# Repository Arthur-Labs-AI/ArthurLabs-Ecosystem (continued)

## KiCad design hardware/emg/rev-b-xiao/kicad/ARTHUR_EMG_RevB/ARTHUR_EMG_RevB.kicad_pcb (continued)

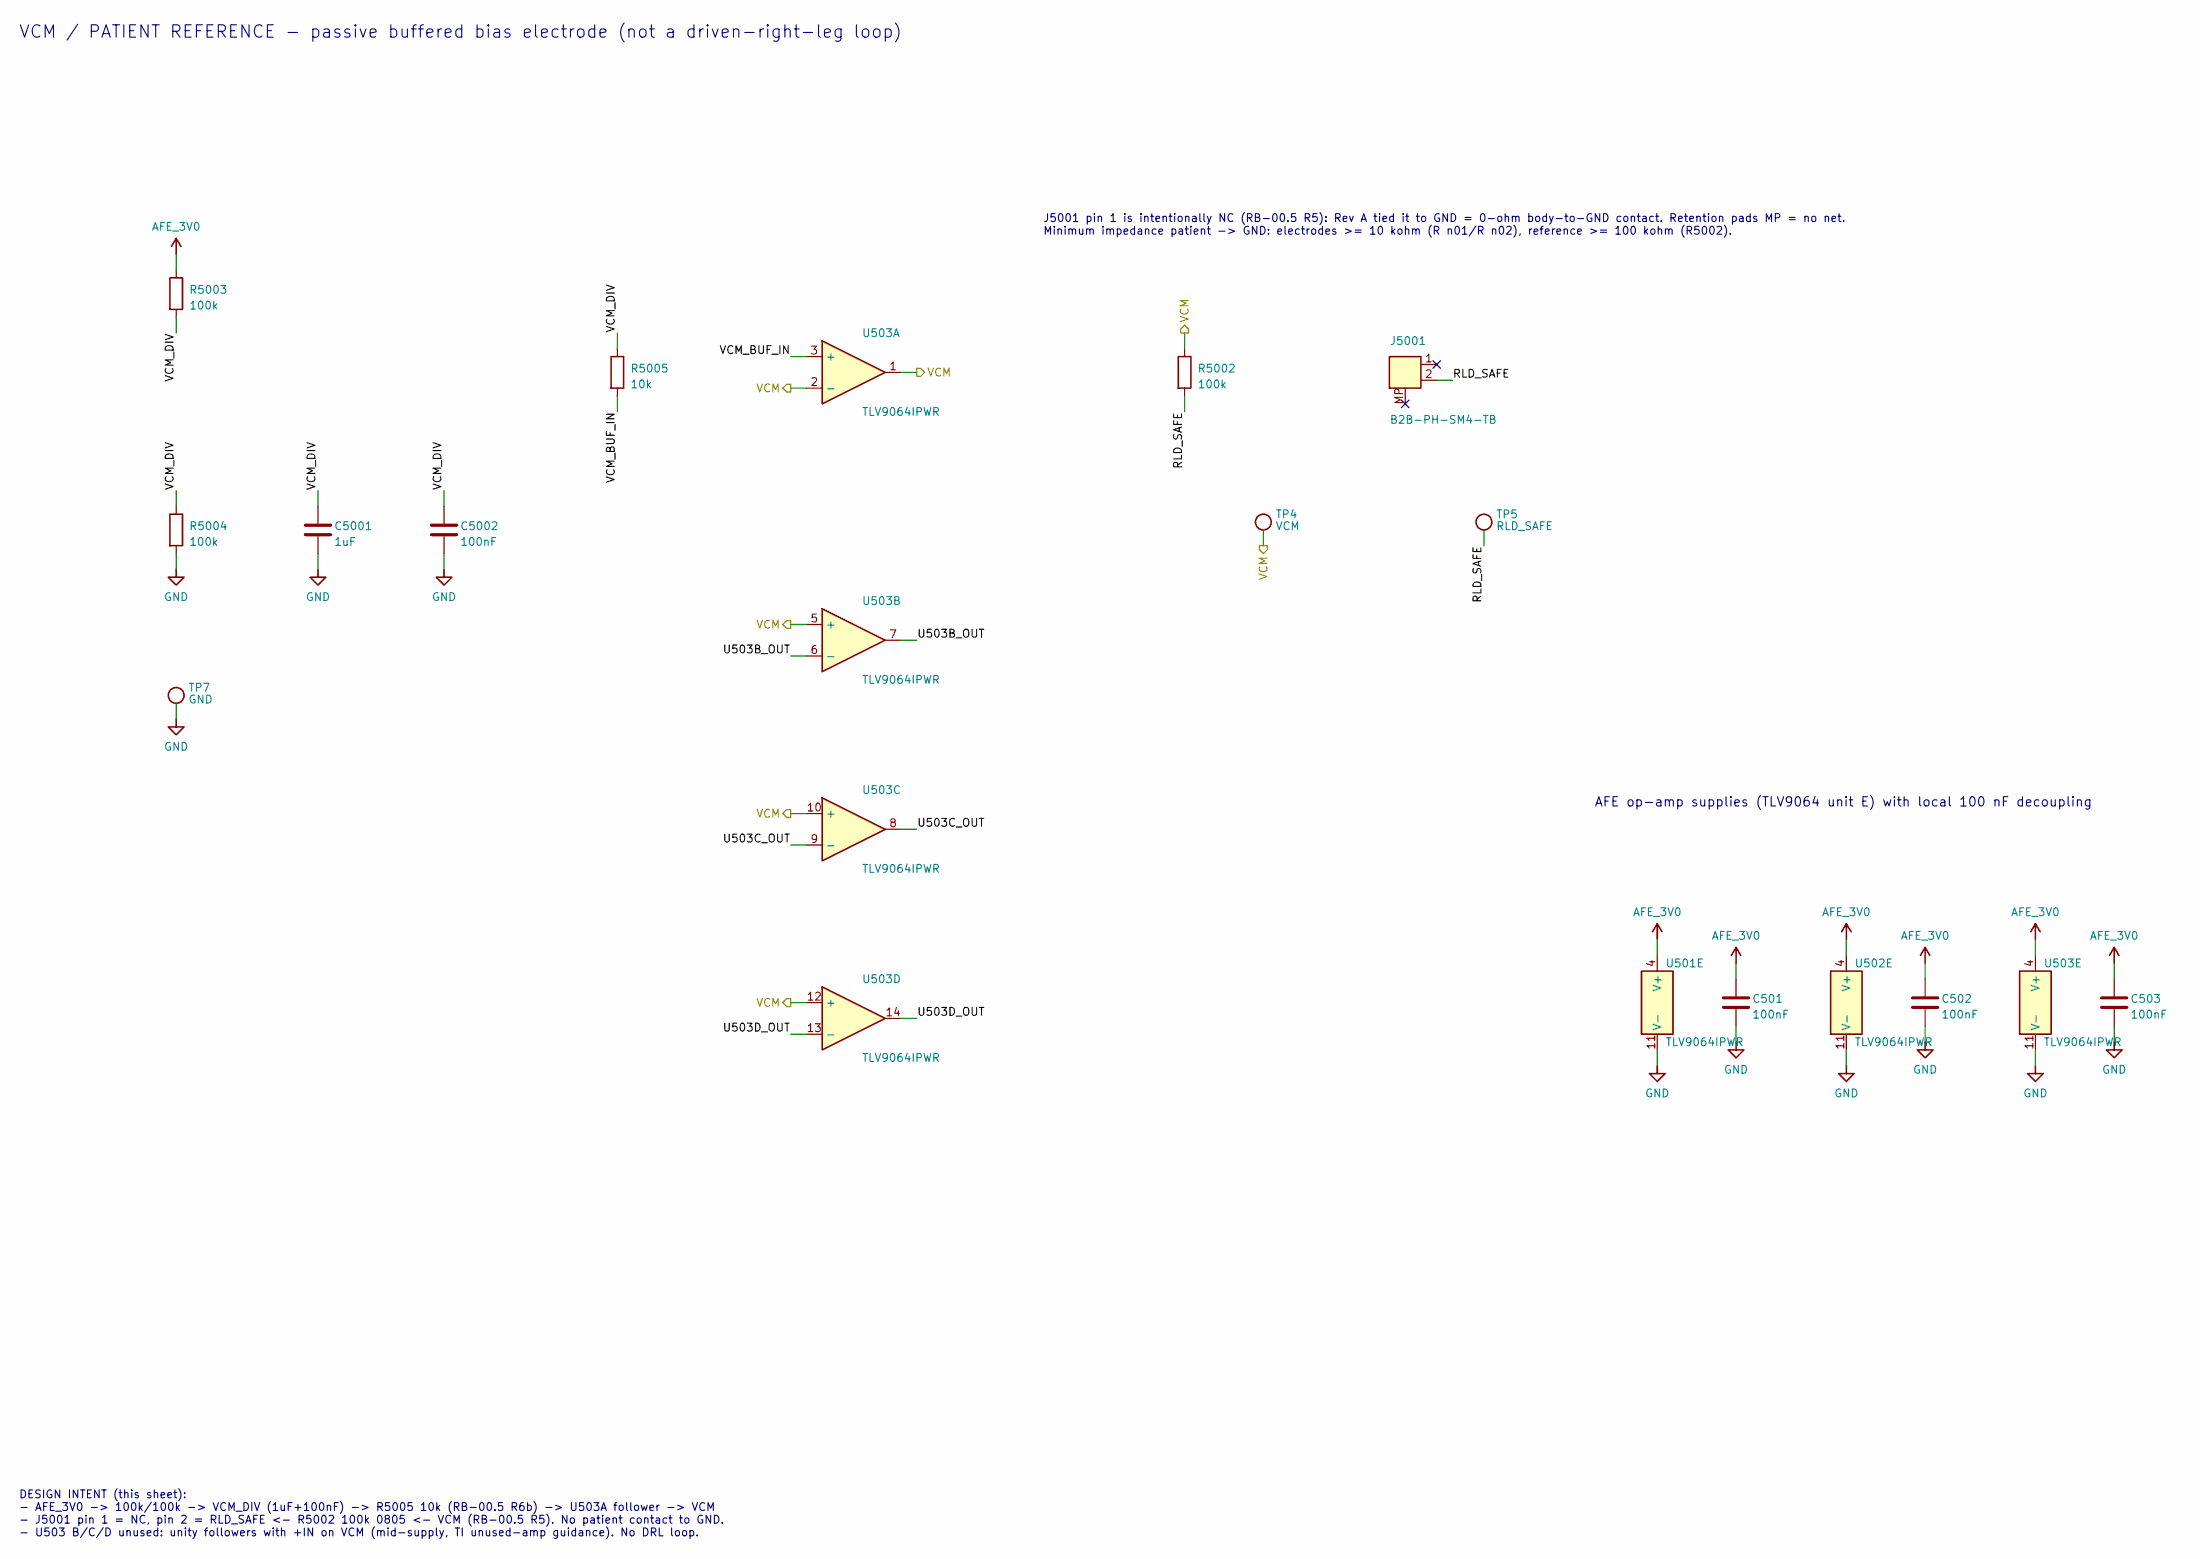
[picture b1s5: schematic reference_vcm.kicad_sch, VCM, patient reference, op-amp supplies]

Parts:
C501, C502, C503, C5002: 100nF; C_0603_1608Metric; MPN CC0603KRX7R9BB104; LCSC C14663
C5001: 1uF; C_0603_1608Metric; MPN CL10B105KO8NNNC; LCSC C59782
J5001: B2B-PH-SM4-TB; JST_PH_B2B-PH-SM4-TB_1x02-1MP_P2.00mm_Vertical; MPN B2B-PH-SM4-TB(LF)(SN); LCSC C160352
R5002: 100k; R_0805_2012Metric; MPN 0805W8F1003T5E; LCSC C149504
R5003, R5004: 100k; R_0603_1608Metric; MPN 0603WAF1003T5E; LCSC C25803
R5005: 10k; R_0603_1608Metric; MPN RC0603FR-0710KL; LCSC C98220
TP4: VCM; TestPoint_Pad_D1.5mm; MPN N/A (bare copper pad); JLC_Class N/A (not assembled)
TP5: RLD_SAFE; TestPoint_Pad_D1.5mm; MPN N/A (bare copper pad); JLC_Class N/A (not assembled)
TP7: GND; TestPoint_Pad_D1.5mm; MPN N/A (bare copper pad); JLC_Class N/A (not assembled)
U501, U502, U503: TLV9064IPWR; TSSOP-14_4.4x5mm_P0.65mm; MPN TLV9064IPWR; LCSC C779410

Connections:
/CH2/BUF_N: U501.13 (-), U501.14; also elsewhere on the board
/CH2/BUF_P: U501.8, U501.9 (-); also elsewhere on the board
/CH2/HIZ_N: U501.12 (+); also elsewhere on the board
/CH2/HIZ_P: U501.10 (+); also elsewhere on the board
/CH4/BUF_N: U502.13 (-), U502.14; also elsewhere on the board
/CH4/BUF_P: U502.8, U502.9 (-); also elsewhere on the board
/CH4/HIZ_N: U502.12 (+); also elsewhere on the board
/CH4/HIZ_P: U502.10 (+); also elsewhere on the board
/Reference_VCM/RLD_SAFE: J5001.2, R5002.2, TP5.1
/Reference_VCM/U503B_OUT: U503.6 (-), U503.7
/Reference_VCM/U503C_OUT: U503.8, U503.9 (-)
/Reference_VCM/U503D_OUT: U503.13 (-), U503.14
/Reference_VCM/VCM_BUF_IN: R5005.2, U503.3 (+)
/Reference_VCM/VCM_DIV: C5001.1, C5002.1, R5003.2, R5004.1, R5005.1
/VCM: R5002.1, TP4.1, U503.1, U503.2 (-), U503.5 (+), U503.10 (+), U503.12 (+); also elsewhere on the board
AFE_3V0: C501.1, C502.1, C503.1, R5003.1, U501.4 (V+), U502.4 (V+), U503.4 (V+); also elsewhere on the board
GND: C501.2, C502.2, C503.2, C5001.2, C5002.2, R5004.2, TP7.1, U501.11 (V-), U502.11 (V-), U503.11 (V-); also elsewhere on the board

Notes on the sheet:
J5001 pin 1 is intentionally NC (RB-00.5 R5): Rev A tied it to GND = 0-ohm body-to-GND contact. Retention pads MP = no net. Minimum impedance patient -> GND: electrodes >= 10 kohm (R n01/R n02), reference >= 100 kohm (R5002).
DESIGN INTENT (this sheet): - AFE_3V0 -> 100k/100k -> VCM_DIV (1uF+100nF) -> R5005 10k (RB-00.5 R6b) -> U503A follower -> VCM - J5001 pin 1 = NC, pin 2 = RLD_SAFE <- R5002 100k 0805 <- VCM (RB-00.5 R5). No patient contact to GND. - U503 B/C/D unused: unity followers with +IN on VCM (mid-supply, TI 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
VCM / PATIENT REFERENCE - passive buffered bias electrode (not a driven-right-leg loop)
AFE op-amp supplies (TLV9064 unit E) with local 100 nF decoupling

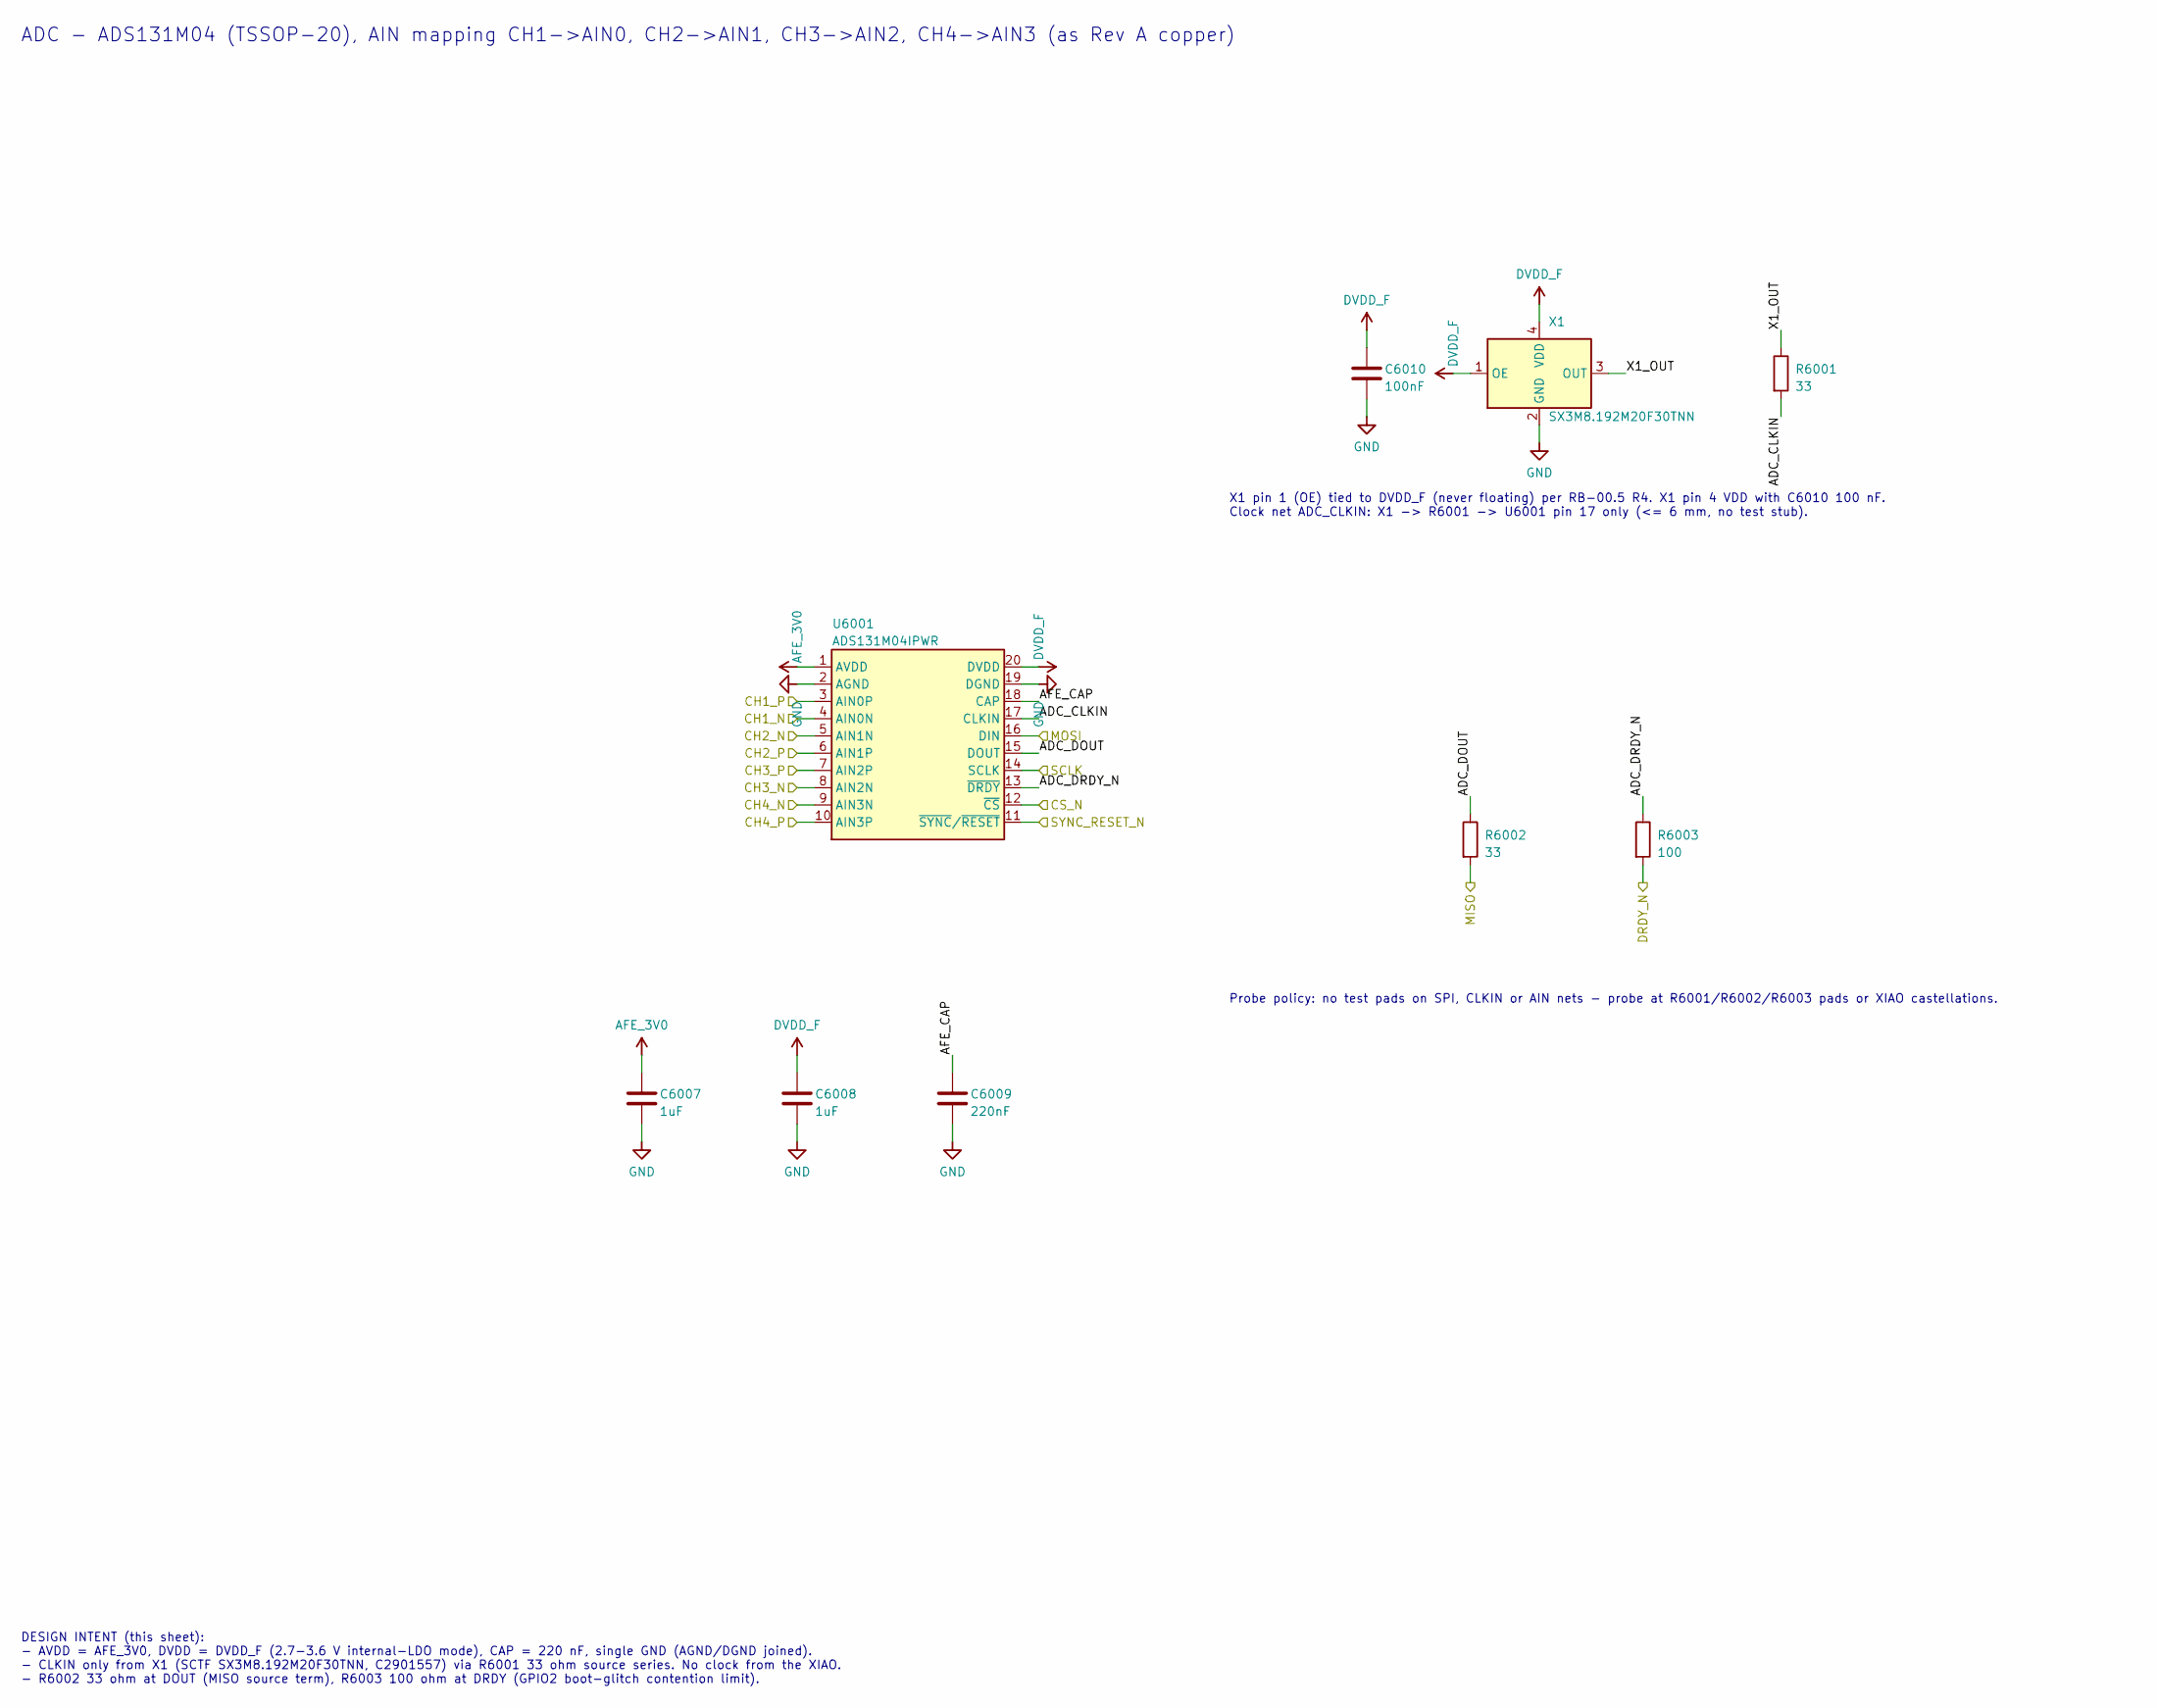
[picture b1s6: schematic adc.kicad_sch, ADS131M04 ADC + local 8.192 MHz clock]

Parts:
C6007, C6008: 1uF; C_0603_1608Metric; MPN CL10B105KO8NNNC; LCSC C59782
C6009: 220nF; C_0603_1608Metric; MPN CL10B224KO8NNNC; LCSC C160828
C6010: 100nF; C_0603_1608Metric; MPN CC0603KRX7R9BB104; LCSC C14663
R6001, R6002: 33; R_0603_1608Metric; MPN 0603WAF330JT5E; LCSC C23140
R6003: 100; R_0603_1608Metric; MPN 0603WAF1000T5E; LCSC C22775
U6001: ADS131M04IPWR; TSSOP-20_4.4x6.5mm_P0.65mm; MPN ADS131M04IPWR; LCSC C2862562
X1: SX3M8.192M20F30TNN; OSC_SCTF_SX3M_SMD3225-4P; MPN SX3M8.192M20F30TNN; LCSC C2901557

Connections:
/ADC/ADC_CLKIN: R6001.2, U6001.17 (CLKIN)
/ADC/ADC_DOUT: R6002.1, U6001.15 (DOUT)
/ADC/ADC_DRDY_N: R6003.1, U6001.13 (~DRDY)
/ADC/AFE_CAP: C6009.1, U6001.18 (CAP)
/ADC/X1_OUT: R6001.1, X1.3 (OUT)
/CH1_N: U6001.4 (AIN0N); also elsewhere on the board
/CH1_P: U6001.3 (AIN0P); also elsewhere on the board
/CH2_N: U6001.5 (AIN1N); also elsewhere on the board
/CH2_P: U6001.6 (AIN1P); also elsewhere on the board
/CH3_N: U6001.8 (AIN2N); also elsewhere on the board
/CH3_P: U6001.7 (AIN2P); also elsewhere on the board
/CH4_N: U6001.9 (AIN3N); also elsewhere on the board
/CH4_P: U6001.10 (AIN3P); also elsewhere on the board
/CS_N: U6001.12 (~CS); also elsewhere on the board
/DRDY_N: R6003.2; also elsewhere on the board
/MISO: R6002.2; also elsewhere on the board
/MOSI: U6001.16 (DIN); also elsewhere on the board
/SCLK: U6001.14 (SCLK); also elsewhere on the board
/SYNC_RESET_N: U6001.11 (~SYNC/~RESET); also elsewhere on the board
AFE_3V0: C6007.1, U6001.1 (AVDD); also elsewhere on the board
DVDD_F: C6008.1, C6010.1, U6001.20 (DVDD), X1.1 (OE), X1.4 (VDD); also elsewhere on the board
GND: C6007.2, C6008.2, C6009.2, C6010.2, U6001.2 (AGND), U6001.19 (DGND), X1.2 (GND); also elsewhere on the board

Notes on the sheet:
DESIGN INTENT (this sheet): - AVDD = AFE_3V0, DVDD = DVDD_F (2.7-3.6 V internal-LDO mode), CAP = 220 nF, single GND (AGND/DGND joined). - CLKIN only from X1 (SCTF SX3M8.192M20F30TNN, C2901557) via R6001 33 ohm source series. No clock from the XIAO. - R6002 33 ohm at DOUT (MISO source term), R6003 1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
ADC - ADS131M04 (TSSOP-20), AIN mapping CH1->AIN0, CH2->AIN1, CH3->AIN2, CH4->AIN3 (as Rev A copper)
Probe policy: no test pads on SPI, CLKIN or AIN nets - probe at R6001/R6002/R6003 pads or XIAO castellations.
X1 pin 1 (OE) tied to DVDD_F (never floating) per RB-00.5 R4. X1 pin 4 VDD with C6010 100 nF. Clock net ADC_CLKIN: X1 -> R6001 -> U6001 pin 17 only (<= 6 mm, no test stub).

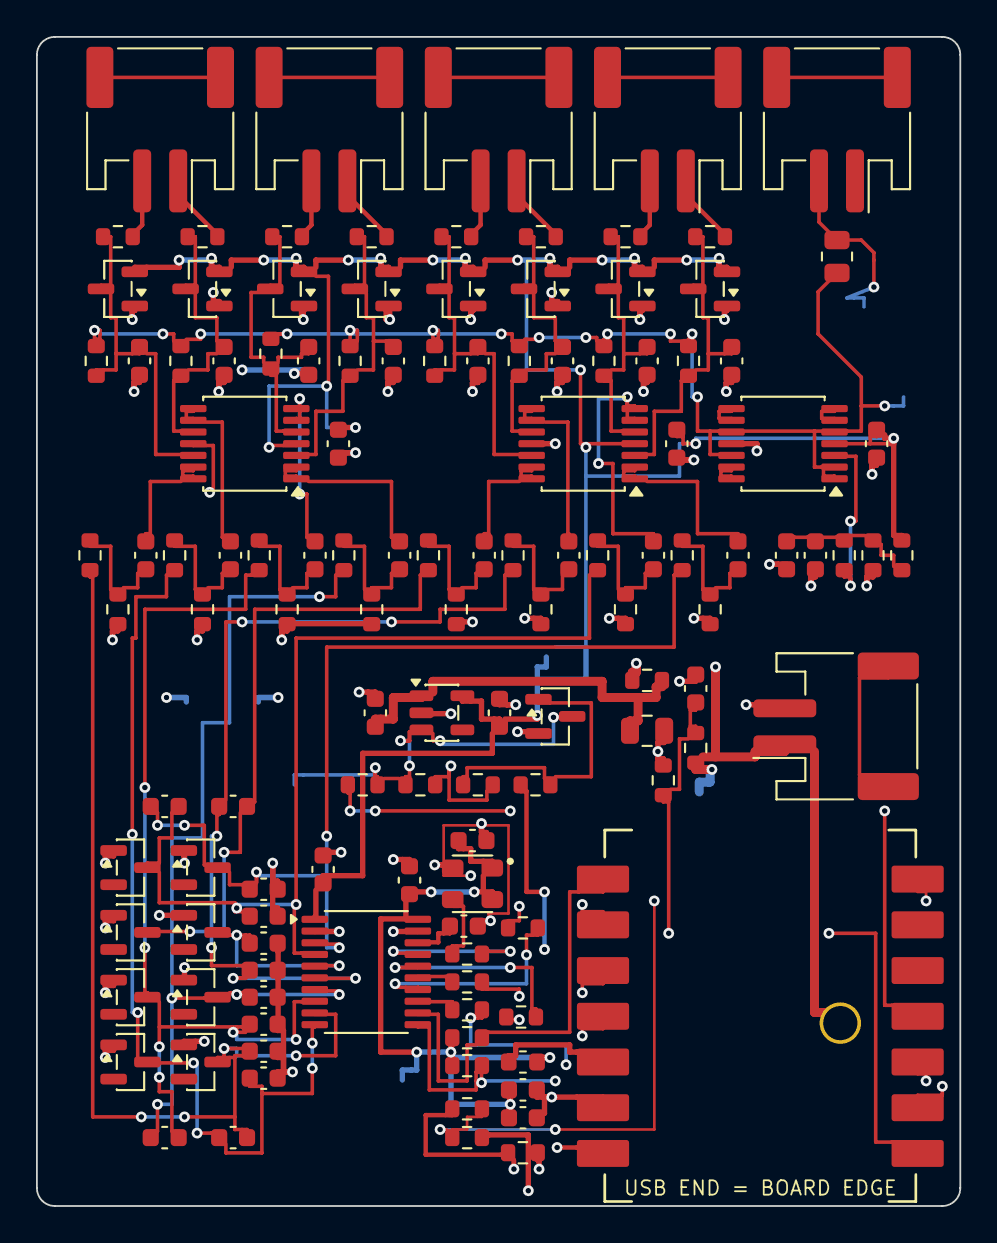
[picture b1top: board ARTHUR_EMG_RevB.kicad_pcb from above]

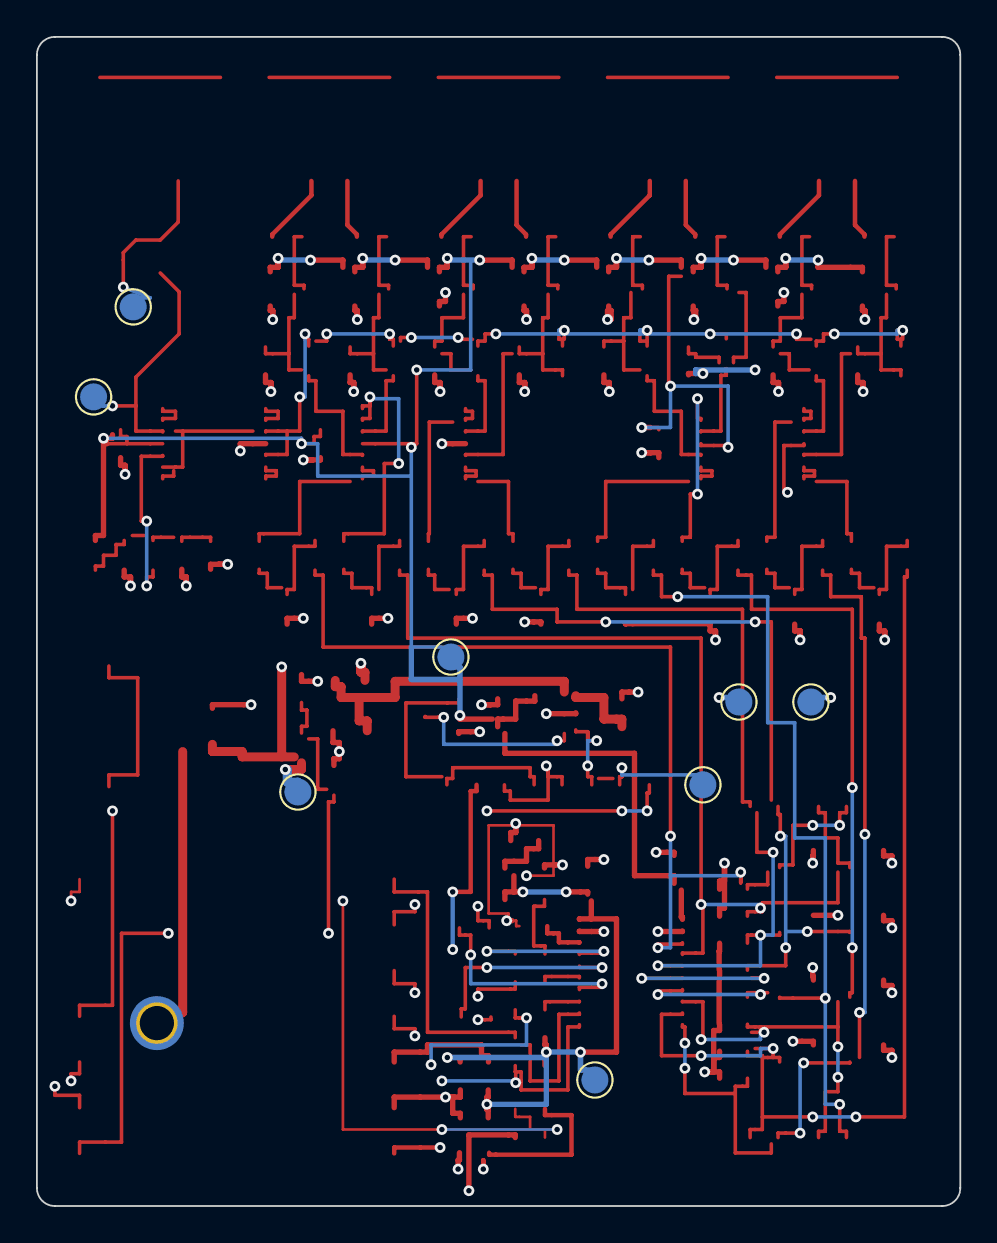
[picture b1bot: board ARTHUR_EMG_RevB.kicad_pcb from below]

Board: 4 copper layers, 51.3 x 65.0 mm, 135 parts (8 on the bottom side), 72 nets.

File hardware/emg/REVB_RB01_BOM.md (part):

# A.R.T.H.U.R EMG Rev B — RB-01 BOM

Source: `kicad-cli sch export bom` on `hardware/emg/rev-b-xiao/kicad/ARTHUR_EMG_RevB/ARTHUR_EMG_RevB.kicad_sch`, grouped by Value + Footprint + MPN + DNP (10.0.6).
**Prices are not re-quoted in RB-01**; see REVB_COST_MODEL.md. No component was substituted to reduce cost.

## Summary

| Metric | Count |
|---|---|
| Components in the netlist | 135 |
| **Populated (JLC-assembled) components** | **126** (R 53, C 43, D 16, J 6, U 5, X 1, Q 1, FB 1) |
| **DNP** | **1** (U1 XIAO ESP32S3: bought retail, hand-soldered per REVB_XIAO_ASSEMBLY_PROCEDURE.md) |
| Bare test pads (not in BOM, not in CPL) | 8 (TP1–TP8) |
| BOM lines | 30 (29 populated + 1 DNP) |
| **Unique exact MPNs (populated)** | **8**: ADS131M04IPWR, TLV9064IPWR, TPS7A2030PDBVR, OT2JI-111-8.192M, BAV199, B2B-PH-SM4-TB(LF)(SN), S2B-PH-SM4-TB(LF)(SN) *(provisional)*, 2N7002 *(generic MPN, any maker)*. Plus Seeed 202003751 (DNP) |
| Generic spec-defined lines | 21 (20 R/C value groups + FB1) |
| **Expected JLC Basic lines** | **21** firm (20 generic R/C/FB + 2N7002); **22** if 10 nF C0G 0603 is Basic |
| **Expected JLC Extended lines** | **7** firm (ADS131M04, TLV9064, TPS7A2030P, X1 C7425393, BAV199 ×16, JST B2B vertical ×5, JST S2B side-entry ×1); **8** if 10 nF C0G is Extended |
| Components with unresolved exact MPN | 21 generic lines (97 parts: 53 R + 43 C + FB1) + J1 provisional + Q3001 maker open + BAV199 packing suffix |

JLC classes are **expected**, taken from REVB_MANUFACTURING_CONSTRAINTS.md §2 and REVB_COST_MODEL.md §1; they are confirmed only when the RB-03 BOM is uploaded.

## BOM lines

| # | References | Qty | Value | Spec | Footprint | MPN | Manufacturer | LCSC | JLC class (expected) | DNP |
|---|---|---|---|---|---|---|---|---|---|---|
| 1 | C101, C102, C201, C202, C301, C302, C401, C402 | 8 | 2.2uF | 2.2uF 16V X7R 0603 MLCC | `Capacitor_SMD:C_0603_1608Metric` | GENERIC (spec-defined; JLC Basic part selected at RB-03) | Any (JLC Basic) | — | Basic (expected) |  |
| 2 | C103, C104, C203, C204, C303, C304, C403, C404 | 8 | 100pF | 100pF 50V C0G 0603 MLCC | `Capacitor_SMD:C_0603_1608Metric` | GENERIC (spec-defined; JLC Basic part selected at RB-03) | Any (JLC Basic) | — | Basic (expected) |  |
| 3 | C105, C205, C305, C405 | 4 | 10nF | 10nF 50V C0G 0603 MLCC | `Capacitor_SMD:C_0603_1608Metric` | GENERIC (spec-defined; JLC Basic part selected at RB-03) | Any (JLC Basic) | — | Basic or Extended (10 nF C0G - confirm) |  |
| 4 | C106, C107, C206, C207, C306, C307, C406, C407 | 8 | 1.0nF | 1.0nF 50V C0G 0603 MLCC | `Capacitor_SMD:C_0603_1608Metric` | GENERIC (spec-defined; JLC Basic part selected at RB-03) | Any (JLC Basic) | — | Basic (expected) |  |
| 5 | C501, C502, C503, C5002, C6010, C7102, C7103 | 7 | 100nF | 100nF 16V X7R 0603 MLCC | `Capacitor_SMD:C_0603_1608Metric` | GENERIC (spec-defined; JLC Basic part selected at RB-03) | Any (JLC Basic) | — | Basic (expected) |  |
| 6 | C4005, C4006, C5001, C6007, C6008 | 5 | 1uF | 1uF 16V X7R 0603 MLCC | `Capacitor_SMD:C_0603_1608Metric` | GENERIC (spec-defined; JLC Basic part selected at RB-03) | Any (JLC Basic) | — | Basic (expected) |  |
| 7 | C4007 | 1 | 22uF | 22uF 10V X5R 0805 MLCC | `Capacitor_SMD:C_0805_2012Metric` | GENERIC (spec-defined; JLC Basic part selected at RB-03) | Any (JLC Basic) | — | Basic (expected) |  |
| 8 | C6009 | 1 | 220nF | 220nF 16V X7R 0603 MLCC | `Capacitor_SMD:C_0603_1608Metric` | GENERIC (spec-defined; JLC Basic part selected at RB-03) | Any (JLC Basic) | — | Basic (expected) |  |
| 9 | C7101 | 1 | 10uF | 10uF 10V X5R 0603 MLCC | `Capacitor_SMD:C_0603_1608Metric` | GENERIC (spec-defined; JLC Basic part selected at RB-03) | Any (JLC Basic) | — | Basic (expected) |  |
| 10 | D101, D102, D103, D104, D201, D202, D203, D204, D301, D302, D303, D304, D401, D402, D403, D404 | 16 | BAV199 | Dual series low-leakage diode, IR <= 5 nA @ 75 V, SOT-23 | `Package_TO_SOT_SMD:SOT-23` | BAV199 | Nexperia | — | Extended (expected), 1 line for all 16 |  |
| 11 | FB1 | 1 | 600R@100MHz | Ferrite bead 600 ohm @ 100 MHz, 0603, >= 200 mA, DCR <= 0.5 ohm | `Inductor_SMD:L_0603_1608Metric` | GENERIC (spec-defined; JLC Basic part selected at RB-03) | Any (JLC Basic) | — | Basic (expected) |  |
| 12 | J1 | 1 | S2B-PH-SM4-TB | JST PH 2.0 mm 2-pin side-entry SMD. Pin 1 = BAT+, pin 2 = BAT- (verify cell lead polarity) | `Connector_JST:JST_PH_S2B-PH-SM4-TB_1x02-1MP_P2.00mm_Horizontal` | S2B-PH-SM4-TB(LF)(SN) (provisional - 'e.g.' in RB-00.6 mounting spec; final at RB-02) | JST | — | Extended (expected) |  |
| 13 | J101, J201, J301, J401, J5001 | 5 | B2B-PH-SM4-TB | JST PH 2.0 mm 2-pin vertical SMD, 2 retention pads | `Connector_JST:JST_PH_B2B-PH-SM4-TB_1x02-1MP_P2.00mm_Vertical` | B2B-PH-SM4-TB(LF)(SN) | JST | — | Extended (expected) |  |
| 14 | Q3001 | 1 | 2N7002 | 60 V N-MOSFET SOT-23, VGS(th) >= 0.8 V | `Package_TO_SOT_SMD:SOT-23` | 2N7002 | Any (JLC Basic, e.g. Nexperia/CJ) | — | Basic (expected) |  |
| 15 | R101, R102, R201, R202, R301, R302, R401, R402, R3006, R3007, R5005, R7104 | 12 | 10k | 10k ±1% 0603 thick film, >=1/10 W | `Resistor_SMD:R_0603_1608Metric` | GENERIC (spec-defined; JLC Basic part selected at RB-03) | Any (JLC Basic) | — | Basic (expected) |  |
| 16 | R103, R104, R203, R204, R303, R304, R403, R404, R3004, R3008, R5003, R5004, R7103, R7105 | 14 | 100k | 100k ±1% 0603 thick film, >=1/10 W | `Resistor_SMD:R_0603_1608Metric` | GENERIC (spec-defined; JLC Basic part selected at RB-03) | Any (JLC Basic) | — | Basic (expected) |  |
| 17 | R105, R106, R205, R206, R305, R306, R405, R406 | 8 | 10M | 10M ±5% 0603 thick film, >=1/10 W | `Resistor_SMD:R_0603_1608Metric` | GENERIC (spec-defined; JLC Basic part selected at RB-03) | Any (JLC Basic) | — | Basic (expected) |  |
| 18 | R107, R108, R207, R208, R307, R308, R407, R408 | 8 | 1.0k | 1.0k ±1% 0603 thick film, >=1/10 W | `Resistor_SMD:R_0603_1608Metric` | GENERIC (spec-defined; JLC Basic part selected at RB-03) | Any (JLC Basic) | — | Basic (expected) |  |
| 19 | R3009 | 1 | 4.7k | 4.7k ±1% 0603 thick film, >=1/10 W | `Resistor_SMD:R_0603_1608Metric` | GENERIC (spec-defined; JLC Basic part selected at RB-03) | Any (JLC Basic) | — | Basic (expected) |  |
| 20 | R4001 | 1 | 4.7 | 4.7 ±1% 0603 thick film, >=1/10 W | `Resistor_SMD:R_0603_1608Metric` | GENERIC (spec-defined; JLC Basic part selected at RB-03) | Any (JLC Basic) | — | Basic (expected) |  |
| 21 | R5002 | 1 | 100k | 100k ±1% 0805 thick film, >=1/10 W, 0805 for creepage | `Resistor_SMD:R_0805_2012Metric` | GENERIC (spec-defined; JLC Basic part selected at RB-03) | Any (JLC Basic) | — | Basic (expected) |  |
| 22 | R6001, R6002, R7101, R7102 | 4 | 33 | 33 ±1% 0603 thick film, >=1/10 W | `Resistor_SMD:R_0603_1608Metric` | GENERIC (spec-defined; JLC Basic part selected at RB-03) | Any (JLC Basic) | — | Basic (expected) |  |
| 23 | R6003 | 1 | 100 | 100 ±1% 0603 thick film, >=1/10 W | `Resistor_SMD:R_0603_1608Metric` | GENERIC (spec-defined; JLC Basic part selected at RB-03) | Any (JLC Basic) | — | Basic (expected) |  |
| 24 | R7106 | 1 | 150k | 150k ±1% 0603 thick film, >=1/10 W | `Resistor_SMD:R_0603_1608Metric` | GENERIC (spec-defined; JLC Basic part selected at RB-03) | Any (JLC Basic) | — | Basic (expected) |  |
| 25 | R7107, R7108 | 2 | 1M | 1M ±1% 0603 thick film, >=1/10 W | `Resistor_SMD:R_0603_1608Metric` | GENERIC (spec-defined; JLC Basic part selected at RB-03) | Any (JLC Basic) | — | Basic (expected) |  |
| 26 | U1 | 1 | XIAO_ESP32S3 | ESP32-S3 module, 21.0 x 17.8 mm, castellated. Headers NOT fitted | `ARTHUR:XIAO_ESP32S3_HANDSOLDER` | Seeed PN 202003751 (XIAO ESP32S3 plain, v1.4, unsoldered-header version) | Seeed Studio | — | N/A - DNP at JLC (bought retail, hand-soldered) | DNP |
| 27 | U501, U502, U503 | 3 | TLV9064IPWR | Quad RRIO op-amp TSSOP-14 | `Package_SO:TSSOP-14_4.4x5mm_P0.65mm` | TLV9064IPWR | Texas Instruments | — | Extended (expected) |  |
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
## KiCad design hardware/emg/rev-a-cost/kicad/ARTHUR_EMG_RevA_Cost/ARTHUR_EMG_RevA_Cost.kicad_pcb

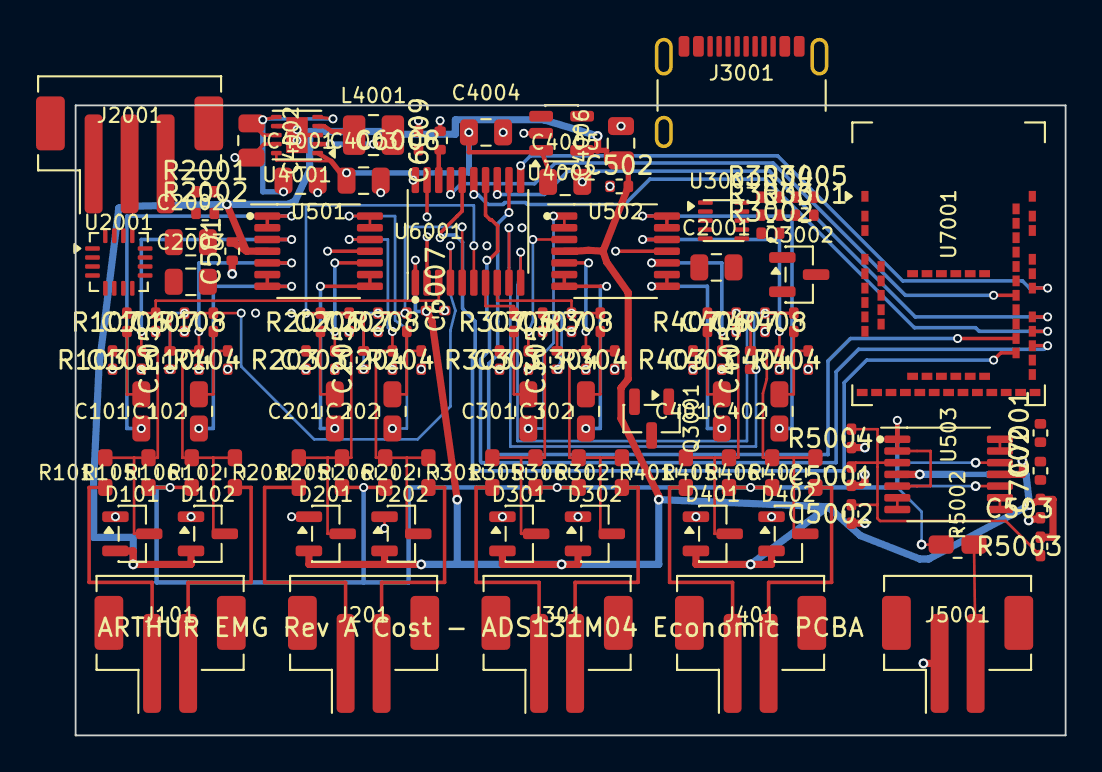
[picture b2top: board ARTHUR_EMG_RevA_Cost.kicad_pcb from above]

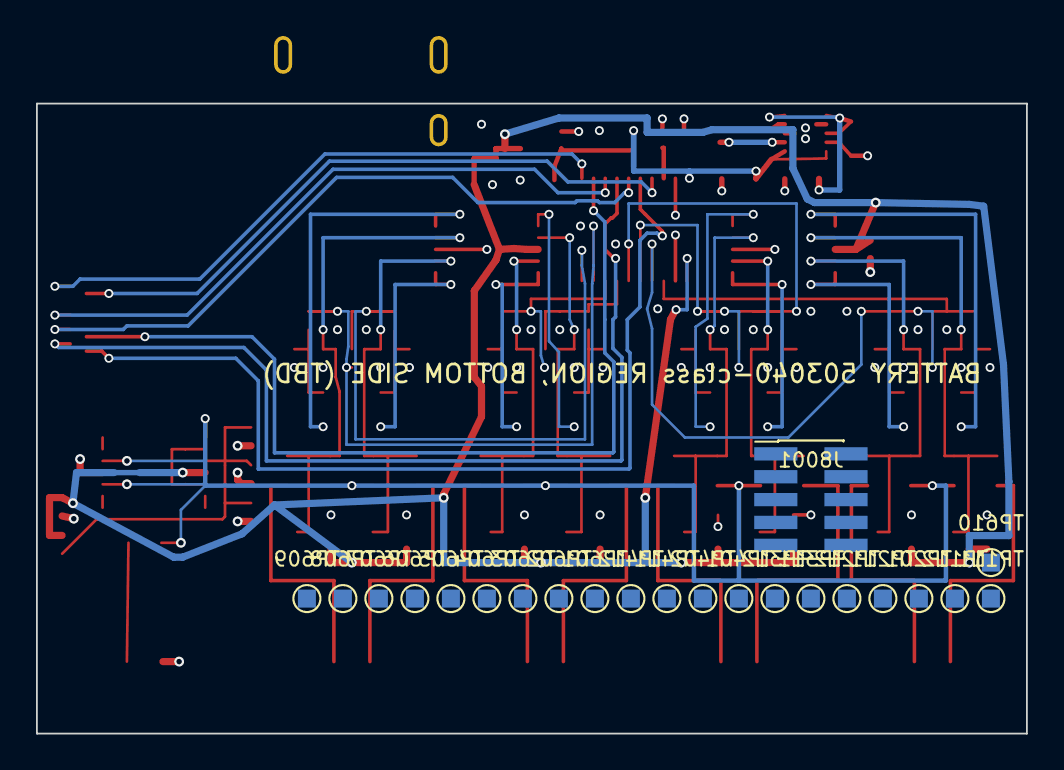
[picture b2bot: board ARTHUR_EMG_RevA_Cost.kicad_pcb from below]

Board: 4 copper layers, 55.0 x 35.0 mm, 138 parts (22 on the bottom side), 76 nets.

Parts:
C101, C102, C201, C202, C301, C302, C401, C402: 2.2uF 16V; C_0603_1608Metric
C103, C104, C203, C204, C303, C304, C403, C404: 100pF 50V C0G; C_0402_1005Metric
C105, C205, C305, C405: 10nF 50V C0G; C_0402_1005Metric
C106, C107, C206, C207, C306, C307, C406, C407: 1.0nF C0G; C_0402_1005Metric
C501, C502, C503, C5002: 0.1uF 16V; C_0402_1005Metric
C2001: 1–10 µF per BQ24074 datasheet; C_0805_2012Metric
C2002, C2003: 4.7–47 µF per BQ24074 datasheet; C_0805_2012Metric
C4001, C4003, C4004: 10 µF (TI typical); C_0805_2012Metric
C4002: 0.1 µF VINA (TI typical); C_0603_1608Metric
C4005, C4006: 1 µF minimum (TPS7A20); C_0603_1608Metric
C5001: 1.0uF 16V; C_0402_1005Metric
C6007, C6008: 1 µF; C_0402_1005Metric
C6009: 220 nF; C_0402_1005Metric
C7001: 4.7 µF typical VDD decoupling (Nordic); C_0402_1005Metric
C7002: TBD local high-frequency decoupling per module la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; C_0402_1005Metric
D101, D102, D201, D202, D301, D302, D401, D402: BAV199; SOT-23
J101, J201, J301, J401: Bipolar EMG electrode connector; JST_PH_B2B-PH-SM4-TB_1x02-1MP_P2.00mm_Vertical
J2001: LiPo pack: BAT+/NTC/GND; JST_PH_B3B-PH-SM4-TB_1x03-1MP_P2.00mm_Vertical
J3001: USB_C_Receptacle_USB2.0_16P; USB_C_Receptacle_GCT_USB4105-xx-A_16P_TopMnt_Horizontal
J5001: Reference electrode connector; JST_PH_B2B-PH-SM4-TB_1x02-1MP_P2.00mm_Vertical
J8001: ARM Cortex Debug 10-pin; PinHeader_2x05_P1.27mm_Vertical_SMD
L4001: 1.5 µH (TI typical circuit; part selection TBD); L_1008_2520Metric
Q3001, Q3002: 2N7002; SOT-23
R101, R102, R201, R202, R301, R302, R401, R402: 10k 1%; R_0603_1608Metric
R103, R104, R203, R204, R303, R304, R403, R404, R3003, R3004, R5003, R5004: 100k 1%; R_0402_1005Metric
R105, R106, R205, R206, R305, R306, R405, R406: 10M 5%; R_0603_1608Metric
R107, R108, R207, R208, R307, R308, R407, R408: 1.0k 1%; R_0402_1005Metric
R2001: 3.57k 1% (250mA 0.5C, KISET=890 typ); R_0402_1005Metric
R2002: 3.24k 1% (500mA USB, KILIM=1610 typ); R_0402_1005Metric
R3001, R3002: 5.1 kΩ (USB Type-C Rd); R_0402_1005Metric
R3005: 100 1%; R_0402_1005Metric
R5002: 100k 1% (Safety Resistor); R_0805_2012Metric
TP111, TP112, TP201, TP211, TP212, TP311, TP312, TP401, TP402, TP411, TP412, TP601, TP602, TP603, TP604, TP605, TP606, TP607, TP608, TP609, TP610: TP_SMD; TP_SMD_1x1mm
U501, U502, U503: TLV9064IPWR; TSSOP-14_4.4x5.0mm_P0.65mm
U2001: BQ24074RGTR; QFN-16-1EP_3x3mm_P0.5mm_EP1.7x1.7mm
U3001: TPD4E05U06DQAR; TPD4E05U06_DQA_2x2mm_P0.5mm
U4001: TPS63031DSKR; TPS63031_DSK0010A_2.5x2.5mm_P0.5mm
U4002: TPS7A2030PDBVR; SOT-23-5
U6001: ADS131M04IPWR; TSSOP-20_4.4x6.5mm_P0.65mm
U7001: MDBT50Q-1MV2; Raytac_MDBT50Q

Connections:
3V3: C4003.1, C4004.1, C4005.1, C6008.1, C7001.1, C7002.1, J8001.1, R3003.1, TP401.1, TP603.1, U4001.1, U4001.10, U4002.1, U6001.20, U7001.28, U7001.30
AFE_3V0: C501.2, C502.2, C503.2, C4006.1, C6007.1, D101.2, D102.2, D201.2, D202.2, D301.2, D302.2, D401.2, D402.2, R3005.2, R5003.2, TP601.1, U501.4, U502.4, U503.4, U4002.5, U6001.1
AFE_CAP: C6009.1, U6001.18
AFE_CLKIN: TP609.1, U6001.17, U7001.43
AFE_DRDY_N: TP608.1, U6001.13, U7001.41
AFE_ENABLE: Q3001.3, R3003.2, U4002.3
AFE_MISO: TP606.1, U6001.15, U7001.39
BAT+: C2003.1, J2001.1, TP201.1, U2001.2, U2001.3
CC1: J3001.A5, R3001.1, U3001.4
CC2: J3001.B5, R3002.1, U3001.5
CH1_N: C105.1, C107.2, R108.2, TP112.1, U6001.4
CH1_P: C105.2, C106.2, R107.2, TP111.1, U6001.3
CH2_N: C205.1, C207.2, R208.2, TP212.1, U6001.5
CH2_P: C205.2, C206.2, R207.2, TP211.1, U6001.6
CH3_N: C305.1, C307.2, R308.2, TP312.1, U6001.8
CH3_P: C305.2, C306.2, R307.2, TP311.1, U6001.7
CH4_N: C405.1, C407.2, R408.2, TP412.1, U6001.9
CH4_P: C405.2, C406.2, R407.2, TP411.1, U6001.10
CHG_N: U2001.9, U7001.45
GND: C103.1, C104.1, C106.1, C107.1, C203.1, C204.1, C206.1, C207.1, C303.1, C304.1, C306.1, C307.1, C403.1, C404.1, C406.1, C407.1, C501.1, C502.1, C503.1, C2001.2, C2002.2, C2003.2, C4001.2, C4002.2, C4003.2, C4004.2, C4005.2, C4006.2, C5001.1, C5002.1, C6007.2, C6008.2, C6009.2, C7001.2, C7002.2, D101.1, D102.1, D201.1, D202.1, D301.1, D302.1, D401.1, D402.1, J2001.3, J3001.A1, J3001.A12, J3001.B1, J3001.B12, J5001.1, J8001.3, J8001.5, J8001.9, Q3001.2, Q3002.2, R103.1, R104.1, R203.1, R204.1, R303.1, R304.1, R403.1, R404.1, R2001.2, R2002.2, R3001.2, R3002.2, R3004.2, R5004.1, TP402.1, TP602.1, U501.11, U502.11, U503.11, U2001.4, U2001.5, U2001.8, U3001.3, U3001.8, U4001.3, U4001.7, U4001.9, U4001.11, U4002.2, U6001.2, U6001.19, U7001.1, U7001.2, U7001.15, U7001.33, U7001.55
ICHG_SET_TBD: R2001.1, U2001.16
ILIM_SET_TBD: R2002.1, U2001.12
MCU_CS_N: TP607.1, U6001.12, U7001.38
MCU_MOSI: TP605.1, U6001.16, U7001.36
MCU_RESET_N: J8001.10, U7001.40
MCU_RESET_N_AFE: TP610.1, U6001.11, U7001.44
MCU_SCLK: TP604.1, U6001.14, U7001.37
unnamed: C101.2, R103.2, R107.1
unnamed: C102.2, R104.2, R108.1
unnamed: C201.2, R203.2, R207.1
unnamed: C202.2, R204.2, R208.1
unnamed: C301.2, R303.2, R307.1
unnamed: C302.2, R304.2, R308.1
unnamed: C401.2, R403.2, R407.1
unnamed: C402.2, R404.2, R408.1
unnamed: C103.2, D101.3, R101.2, R105.2, U501.3
unnamed: C104.2, D102.3, R102.2, R106.2, U501.5
unnamed: C203.2, D201.3, R201.2, R205.2, U501.10
unnamed: C204.2, D202.3, R202.2, R206.2, U501.12
unnamed: C303.2, D301.3, R301.2, R305.2, U502.3
unnamed: C304.2, D302.3, R302.2, R306.2, U502.5
unnamed: C403.2, D401.3, R401.2, R405.2, U502.10
unnamed: C404.2, D402.3, R402.2, R406.2, U502.12
unnamed: J101.1, R101.1
unnamed: J101.2, R102.1
unnamed: J201.1, R201.1
unnamed: J201.2, R202.1
unnamed: J301.1, R301.1
unnamed: J301.2, R302.1
unnamed: J401.1, R401.1
unnamed: J401.2, R402.1
unnamed: Q3002.3, R3005.1
unnamed: C101.1, U501.1, U501.2
unnamed: C102.1, U501.6, U501.7
unnamed: C201.1, U501.8, U501.9
unnamed: C202.1, U501.13, U501.14
unnamed: C301.1, U502.1, U502.2
unnamed: C302.1, U502.6, U502.7
unnamed: C401.1, U502.8, U502.9
unnamed: C402.1, U502.13, U502.14
unnamed: C5001.2, C5002.2, R5003.1, R5004.2, U503.3
unnamed: U503.6, U503.7
unnamed: U503.8, U503.9
unnamed: U503.13, U503.14
PACK_NTC: J2001.2, U2001.1
PGOOD_N: U2001.7, U7001.48
RLD_SAFE: J5001.2, R5002.2
SWDCLK: J8001.4, U7001.53
SWDIO: J8001.2, U7001.51
SW_L1: L4001.1, U4001.4
SW_L2: L4001.2, U4001.2
SYS_RAW: C2002.1, C4001.1, C4002.1, U2001.6, U2001.10, U2001.11, U4001.5, U4001.6, U4001.8
USB_D+: J3001.A6, J3001.B6, U3001.1, U7001.35
USB_D-: J3001.A7, J3001.B7, U3001.2, U7001.34
USB_VBUS: C2001.1, J3001.A4, J3001.A9, J3001.B4, J3001.B9, Q3001.1, Q3002.1, R3004.1, U2001.13, U7001.32
VCM: R105.1, R106.1, R205.1, R206.1, R305.1, R306.1, R405.1, R406.1, R5002.1, U503.1, U503.2, U503.5, U503.10, U503.12
